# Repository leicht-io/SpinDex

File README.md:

# SpinDex
SpinDex is a small RPM measurement tool for the Beogram 4000 series.
The main focus is to verify that the turntable is restored correctly and maintains the correct speed over an extended period.
The code is written to run on the M5Stack StampS3 (ESP32-S3) but could easily be ported to other microcontrollers and architectures.

This mono repository is divided into multiple sub-repositories, explained below:

### 3D Files (3d-files):
This folder contains the printable enclosure:
- `spindex_bottom.stl`: the base. It holds the electronics and sensor, and its curved jaw hooks onto the turntable chassis.
- `spindex_top.stl`: the lid.
- `spindex_spacer.stl`: an optional insert (about 2.8 mm thick) that clips into the base's jaw. The chassis width differs between production variants of the Beogram 4000, 4002 and 4004: print the base as-is for one width, and add the spacer to fit the other.

| Exploded: lid, base and spacer | Assembled with the spacer fitted |
|---|---|
|  |  |

---

### Web App (web-app)
This folder contains the web app. It connects to the controller over Bluetooth (Web Bluetooth) or a USB cable (Web Serial), with nothing to install, and records, organises and compares RPM measurements. It's hosted publicly, free to use, at **https://spindex.leicht.io/**.

Features:
- **Desktop-style layout**: a menu bar (File / Measurement / View), a library sidebar and a status bar showing the link (Bluetooth or USB) and the sensor's firmware version, a live recording readout, the app version and a clock.
- **Bluetooth or USB**: pick how to connect from the connection menu at the top right. Picking one drops the other, so readings are never recorded twice. The status bar warns when the sensor is connected but sends no readings.
- **Turntable folders**: measurements are grouped per turntable, identified by model and serial number (e.g. "Beogram 4002 · SN 2145678"). Pick or create the turntable when starting a measurement; typing an existing model/serial files it with the earlier runs. Search the library by name or serial.
- **Recording**: start/stop measurements, persisted locally in the browser (IndexedDB), so a page refresh or reconnect doesn't lose a running session. Automatic reconnect rides out a dropped Bluetooth link during an unattended run. Over USB, a cable pulled mid-session reconnects by itself when it's plugged back in, and a page reload during a recording picks the sensor back up without the picker. Otherwise an idle tab leaves the port alone for other tools.
- **Measurement view**: current/average/peak readouts with their deviation from the nominal 33⅓/45 RPM on a small gauge, colour-coded by how far off spec, plus a chart that zooms to the measured range and marks the nominal speed.
- **Chart time windows** (Live 10 min / 1h / 6h / 12h / 24h / All), auto-bucketed to a fixed point budget so even a 24h session stays smooth.
- **Gap-aware charting**: a disconnect or closed tab shows as a marked gap rather than a misleading flat or interpolated line.
- **Compare**: overlay up to eight measurements aligned by time since start (e.g. before/after a belt change), with a hover readout and a stats table: mean, drift from nominal, rev-to-rev standard deviation, min and max, ignoring spin-up and stopped readings.
- **Organise**: rename, move between folders, export as CSV, delete.
- **Connection help**: a dialog explains how to connect over Bluetooth and over USB on the current platform, with a table of which browsers support each. Browsing and comparing saved measurements works in any browser; only recording needs Web Bluetooth or Web Serial.
- **Changelog**: click the version in the status bar.
- **Sensor firmware updates**: *Update sensor firmware…* in the connection menu flashes firmware over USB, through the chip's own bootloader, so it works whatever the sensor runs now. It offers every firmware release: the one for this version of the app by default, or an older one to downgrade (see below).
- Works from phone to desktop: below 900px the library becomes a drawer, and below 720px the menus fold into one overflow menu.
- Dark, instrument-style design after the leicht.io look: IBM Plex Sans / Plex Mono and a copper accent.

Browser support for recording:

| Browser | Platforms | Bluetooth (Web Bluetooth) | USB (Web Serial) |
|---|---|---|---|
| Google Chrome | Windows 10+, macOS, ChromeOS | ✓ | ✓ |
| Google Chrome | Linux | behind `chrome://flags/#enable-experimental-web-platform-features`, BlueZ 5.41+ | ✓ (needs access to `/dev/ttyACM*`, usually the `dialout` group; see the note below) |
| Google Chrome | Android 6+ | ✓ | only on some newer devices |
| Microsoft Edge | Windows, macOS | ✓ | ✓ |
| Firefox | Windows, macOS, Linux | ✕ | ✓ (151+) |
| Opera | Windows, macOS, Linux | ✕ | ✓ |
| Samsung Internet, Opera | Android | ✓ | ✕ |
| Bluefy | iPhone, iPad | ✓ (third-party app) | ✕ |
| Safari | all | ✕ | ✕ |

USB needs firmware built from this repository at or after USB support was added (see the µController section). Older firmware connects over USB but sends no readings. In the port picker the sensor is listed as *USB JTAG/serial debug unit*, a name fixed in the ESP32-S3 (see the µController section).

Chrome on Linux, in versions before Chromium's September 2026 fix, can drop the port the moment it opens it (the app says "the port was dropped right after opening it"). That happens after a pyserial-based tool (PlatformIO's upload or `pio device monitor`, esptool) has used the port, because those tools leave it with `VMIN=0` and Linux keeps that setting for the next program. Run `stty -F /dev/ttyACM0 min 1` and connect again. A PlatformIO upload does this for you (see below).

Measurements are stored per browser; export as CSV to move them elsewhere.

Development, from `web-app/`:
- `yarn start`: dev server (HTTPS, required for Web Bluetooth and Web Serial).
- `yarn build`: production build.
- `yarn test`: unit tests for the pure logic (chart bucketing/gap detection, CSV export, measurement stats, folder grouping, USB serial line parsing, changelog/version consistency).

Releases are listed in `web-app/app/core/changelog.ts`. Its newest entry must match the `version` in `web-app/package.json` (a unit test checks this), so bump both together.

`yarn build` also builds the sensor firmware from your working copy with PlatformIO (`pio` on the PATH, its own install in `~/.platformio`, or `PIO=/path/to/pio`). It puts the firmware in `dist/firmware/<version>/`, where the firmware updater loads it from, next to the older releases' firmware from GitHub if GitHub can be reached. `dist/` is gitignored, so this build is only for deploying or serving from your machine; released builds come from the Release workflow below. Browsers can't download GitHub release files from another site, so the app serves all firmware itself. `yarn build:web` builds the app alone.

#### Releases

Releases are automatic, driven by [conventional commits](https://www.conventionalcommits.org/) on master (`.github/workflows/release.yml`):

1. After each push to master, the *Release* workflow opens or updates a **release PR**. It bumps the version from the commits since the last release (`feat`: minor; `fix`, `perf`: patch; `feat!:` or a `BREAKING CHANGE:` footer: major; `docs`, `chore`, `ci`, `test` and `refactor` don't release) and drafts the entry in `web-app/app/core/changelog.ts` from the commit subjects.
2. Edit that entry into user-facing wording (the app shows it as release notes), then merge the PR. Once you've pushed to the PR, the workflow leaves it alone.
3. The merge publishes the release: tests, the `v<version>` tag, and a GitHub release with notes from the changelog. It carries the firmware files (for the updater, and for flashing by hand) and `spindex-web-<version>.zip`, the built app with every firmware release in it.
4. Upload the contents of that zip to the host.

A version bumped by hand (in `package.json` and `changelog.ts`) is published the same way once it reaches master. With squash merges, the PR title becomes the commit, so give PRs conventional titles too.

The workflow needs, under *Settings → Actions → General → Workflow permissions*, "Read and write permissions" and "Allow GitHub Actions to create and approve pull requests". The *CI* workflow (`.github/workflows/ci.yml`) checks every pull request: types, lint, tests and builds of the app and the firmware. Release PRs opened by the bot don't trigger it (GitHub doesn't run workflows for its own token's PRs), so publishing runs the tests itself. Dependabot (`.github/dependabot.yml`) proposes npm and Actions updates weekly.

To try updates with `yarn start`, run `yarn firmware:local` (the working copy's firmware, as `yarn build` bundles it) or `yarn firmware` (only the GitHub releases) first; without either, the updater says the build has no firmware.

---

### µController Source Code (controller-source)
This folder contains the source code for the microcontroller. The RPM edge-counting/calculation logic is split out into a hardware-free class (`src/logic/RpmCounter`) with its own unit tests, runnable on the host (no board needed) via `pio test -e native`.

Every 500 ms the firmware sends the current RPM two ways: as a Bluetooth notification, and as a line like `rpm:33.33` on the StampS3's own USB-C port. The web app reads those lines over Web Serial, and `pio device monitor` or the Arduino Serial Plotter can show them too.

The firmware's version is the web app's: `scripts/firmware_version.py` reads it from `web-app/package.json` at build time, so a release bumps one number (see the web app section) and the sensor reports the version of the app it shipped with. The web app reads it on connecting and shows it in the status bar. Over Bluetooth it's the Firmware Revision String (`0x2A26`) in the standard Device Information Service (`0x180A`). Over USB the app sends a `version` line and the firmware answers with a line like `version:2.3.0`, which it also prints on startup. You can type `version` into `pio device monitor` to check it. Firmware from before 2.3.0 doesn't report a version, and the app shows it as unknown. Firmware built without `web-app/package.json` next to it reports `unversioned`.

USB uses the ESP32-S3's built-in USB-Serial/JTAG unit (`ARDUINO_USB_CDC_ON_BOOT` in `platformio.ini`), which keeps uploads button-free. Its name, "USB JTAG/serial debug unit", is fixed in the chip. Only the USB-OTG controller (TinyUSB) could call the device "SpinDex", but on the pinned Arduino core its reboot-to-bootloader hangs the board, so every upload would need the G0 button.

After each upload, `scripts/restore_tty.py` sets the port back to `VMIN=1` on Linux so Chrome can read it (see the Linux note in the web app section). After using `pio device monitor`, run `stty -F /dev/ttyACM0 min 1` yourself.

A browser connected to the sensor holds its port, so choose **Disconnect** in the app (or close it) before uploading.

`pio run -t webbundle` (with `SPINDEX_FIRMWARE_DIR` set) copies what an upload flashes into a folder, with a `manifest.json` of offsets and flash settings: bootloader, partition table, `boot_app0` and the app. The *Release* workflow runs it for each release and attaches the result to the GitHub release; `yarn firmware:local` runs it on the working copy. The web app's updater flashes exactly that set with esptool-js. Writing `boot_app0` resets which app slot boots, so the sensor always starts the image just written. The manifest carries each image's size and SHA-256, which the app checks after downloading (a missing or stale file is never flashed), and esptool-js reads every image back from flash to verify it. Before writing, the updater checks the board is an ESP32-S3 with 8 MB of flash, since other ESP32-S3 boards share the SpinDex's USB IDs.

---

### Documentation (documentation)
This folder contains the [sensor pin setup and wiring diagram](documentation/pinSetup.md). The PCB schematics themselves live in `hardware/carrier-board`, below.

---

### Hardware (hardware/carrier-board)
This folder contains the custom carrier board PCB design (KiCad) that
piggybacks the M5Stack StampS3 module and the TCRT5000 IR sensor front end
on a single board. See its own [README](hardware/carrier-board/README.md)
for the schematic writeup, BOM, and what's left before fabrication.

---

Please note that this project is in progress and prone to change. The following tasks needs to be implemented before i consider the SpinDex finished.

- tests (started — see the web app's `yarn test` and the µController's `pio test -e native`; coverage is still thin, mostly the pure logic so far).
- custom-made PCB (in progress, see `hardware/carrier-board` — not yet routed or fabricated).

Feel free to develop further on the project and create PRs if, necessary. I would be happy to cooperate with others on the device.

More pictures and background: [SpinDex on leicht.io](https://leicht.io/restoration-services#spindex).

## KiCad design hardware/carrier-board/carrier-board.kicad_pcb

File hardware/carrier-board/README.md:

# SpinDex Carrier Board

A custom PCB that piggybacks the M5Stack STAMP-S3M module on one side and
implements the TCRT5000 reflective IR sensor + comparator circuit directly
on the other, replacing the hand-wired FC-51/TCRT5000 breakout + jumper
wires with a single board sized to mount precisely against the Beogram's
strobe ring.

Built with KiCad 9. Everything in this folder was generated by script (see
"How this was built" below) and validated with `kicad-cli` (ERC/DRC both
pass clean) — **but it has not been opened in the KiCad GUI or physically
verified yet.** Do the checks in "Before you fabricate" first.

## Files

- `carrier-board.kicad_pro` / `.kicad_sch` / `.kicad_pcb` — the project
- `spindex.kicad_sym` — custom symbols: `STAMP-S3M`, `TCRT5000`
- `spindex.pretty/STAMP-S3M_DIP28_P1.27mm.kicad_mod` — custom footprint
- `sym-lib-table` / `fp-lib-table` — project-local library table, adds only
  the `spindex` library; everything else (Device, Comparator, OptoDevice,
  Connector_JST, etc.) resolves from KiCad's standard global libraries

## What's verified vs. estimated

**Verified directly from primary sources:**
- STAMP-S3M's full 28-pin pinout (pin number → signal name) — read
  directly from M5Stack's own module schematic
  ([Sch_M5StampS3_v0.2.pdf](https://m5stack-doc.oss-cn-shenzhen.aliyuncs.com/522/Sch_M5StampS3_v0.2.pdf))
- 1.27mm pin pitch, 26×18×5mm module body (M5Stack docs/product listings)
- TCRT5000 pin assignment (1=Collector, 2=Emitter, 3=Anode, 4=Cathode) —
  read directly from the [Vishay TCRT5000 datasheet](https://www.vishay.com/docs/83760/tcrt5000.pdf)'s
  top-view pin diagram
- The `OptoDevice:Vishay_TCRT5000` footprint is KiCad's own standard
  library part for this exact component — not custom-made

**NOT verified — check before fabricating:**
- **Row-to-row pad spacing on `STAMP-S3M_DIP28_P1.27mm`, set to 15.24mm.**
  No source gives this dimension; it's sized to fit inside the module's
  known 18mm body width with plausible margin, nothing more. **Measure the
  actual module with calipers and update `ROW_SPACING` in
  `gen_footprint.py` (or edit the footprint directly) before ordering
  boards.** Getting this wrong means the module's pins won't line up with
  the holes.

## The circuit

- **Power:** none of this board's business, deliberately. The M5StampS3
  module (the assembled product, not just the bare chip-module inside it)
  has its own onboard USB-C connector and 5V→3.3V regulator — confirmed
  from M5Stack's own schematic, which shows the USB-C port, ESD protection,
  and DCDC regulator as part of the same board the 28-pin header lives on.
  Power it over USB-C like you would to flash it, and its `3V3` pin (typed
  `power_out` in the symbol, since the module is genuinely sourcing that
  rail) feeds the sensor circuit directly. `5V` on the header is a no-connect
  here — it's an available breakout on the module, not something this board
  drives. There's no separate power connector or regulator on this board at
  all; earlier drafts had a JST-PH power input and a bulk cap, both removed
  once it was clear the module's own USB-C already covers it.
- **Sensor front end:** D1 (TCRT5000) — R1 (220Ω) limits the IR LED
  current; R2 (10kΞ) pulls the phototransistor's collector up to 3V3,
  forming a voltage divider whose node (`PHOTO_C`) swings toward GND when
  a reflective bar is under the sensor.
- **Comparator:** U2 (LM393, referenced via its base `LM2903` symbol —
  same part, see below) compares `PHOTO_C` against a threshold set by
  RV1 (10kΩ trimmer, wired 3V3–GND with the wiper feeding the comparator's
  `-` input). Output idles HIGH (pulled up by R4) and drops LOW when a
  reflective bar is detected — **same polarity as the wired TCRT1000/FC-51
  setups this replaces, so `arduino_target.ino`'s edge-detection logic
  works unchanged.** The comparator's second (unused) gate has both inputs
  tied to GND so it can't float/oscillate; its output is left unconnected.
- **Status LED:** D2 + R3, lights when the sensor output is LOW (i.e. a
  bar is detected) — handy for bench-checking alignment without a scope.
- **EN/Boot pull-ups, no buttons:** R5 (10kΩ, `EN`) and R6 (10kΩ, `G0/Boot`)
  hold both pins at a defined HIGH so the module boots and runs normally.
  No manual reset/boot-select switches on this board — flashing means
  reconnecting USB-C to the module directly (same as any bare module),
  not pressing a button here.

### Why `Comparator:LM2903` instead of `LM393`

KiCad's `LM393` symbol is defined via `(extends "LM2903")` — it only holds
property overrides and depends on `LM2903`'s own graphics/pins to actually
render. Referencing `LM2903` directly avoids needing to also embed the
base symbol just to satisfy the alias, while remaining the same physically
interchangeable dual-comparator part; the schematic's `Value` field is set
to "LM393" so the BOM reads correctly.

## Layout

Two zones, as asked for — StampS3 on the left, TCRT5000 + comparator front
end on the right, on one board:

```
[R5]                        [D1 TCRT5000]
[R6]       [U1 STAMP-S3M]   [R1][R2]
                            [RV1]
                            [U2 LM393][C2]
                            [R4][R3]
                            [D2 status]
```

The board outline is currently just a bounding rectangle around all
components with room to breathe — **not a final shape.** Once the
enclosure is designed (or if it already exists in `../../3d-files/`),
reshape `Edge.Cuts` in the PCB editor so the sensor end sits where the
enclosure needs it relative to the platter, then trim the rest of the
board down from there.

## Before you fabricate

1. **Measure the actual STAMP-S3M module with calipers** and correct
   `ROW_SPACING` in `spindex.pretty/STAMP-S3M_DIP28_P1.27mm.kicad_mod` if
   it doesn't match 15.24mm.
2. **Open in KiCad and run "Update PCB from Schematic"** (Tools menu, or
   the equivalent toolbar button) — this syncs the netlist from the
   ERC-clean schematic onto the PCB and lights up the ratsnest. This
   wasn't done here on purpose: hand-duplicating the netlist into the PCB
   file risked a silent mismatch between the two; letting KiCad's own
   sync do it means there's exactly one source of truth (the schematic).
3. **Route the board.** Nothing is routed yet — only placed. A scripted
   auto-routing attempt was made (A* pathfinding with F.Cu/B.Cu+via
   fallback for congested spots) and got every net to *find* a path with
   0 unconnected nets, but kept surfacing new clearance/via-crowding
   violations faster than they could be cleanly resolved blindly —
   routing is fundamentally an interactive, visual-feedback problem
   (that's why every PCB tool has a live-DRC GUI for it) in a way
   placement and schematic capture weren't, and continuing to iterate
   on it without that feedback stopped being productive. With 12
   components and mostly low-speed signals this is a reasonable board to
   route by hand in an evening — KiCad's interactive router (push-and-
   shove, hotkey `X`) makes this fast once nets are synced from the
   schematic (step 2). There's no RF-critical routing here *except* keep
   the area over the STAMP-S3M module's antenna (top-right corner of its
   footprint, matching its silkscreen orientation) clear of copper and
   other components per M5Stack's own schematic — check their PDF for
   the exact keepout if you want to be precise about it. Also worth
   knowing: the layout was widened from an earlier pass to make room
   once real pad sizes were checked (routing revealed the initial
   spacing was tighter than the components actually need) — reasonable
   starting positions, not final.
4. **Tidy the schematic visually.** It's electrically correct (0 ERC
   violations) but was laid out programmatically — labels and component
   text overlap in places. Purely cosmetic; a few minutes of dragging
   things apart in the schematic editor fixes it, no netlist risk.
5. Reshape the board outline to the final enclosure, as above.
6. Re-run `kicad-cli sch erc` / `kicad-cli pcb drc` after any changes.

## BOM

| Ref | Part | Value | Footprint |
|---|---|---|---|
| U1 | M5Stack STAMP-S3M | — | `spindex:STAMP-S3M_DIP28_P1.27mm` |
| D1 | Vishay TCRT5000 | — | `OptoDevice:Vishay_TCRT5000` |
| U2 | LM393 (or LM2903) | dual comparator | `Package_DIP:DIP-8_W7.62mm` |
| RV1 | Trimmer potentiometer | 10kΩ | `Potentiometer_THT:Potentiometer_Bourns_3296W_Vertical` |
| R1, R3 | Resistor | 220Ω | `Resistor_THT:R_Axial_DIN0207_L6.3mm_D2.5mm_P10.16mm_Horizontal` |
| R2, R4, R5, R6 | Resistor | 10kΩ | same |
| C2 | Ceramic capacitor | 100nF | `Capacitor_THT:C_Disc_D3.0mm_W2.0mm_P2.50mm` |
| D2 | LED (status) | — | `LED_THT:LED_D3.0mm` |

All through-hole, hand-solder friendly. No power connector, regulator, or
buttons on this board — power and programming both go through the
M5StampS3 module's own USB-C port. Total BOM cost is a couple of dollars
in passives plus the STAMP-S3M module and TCRT5000 sensor themselves.

## How this was built

Every file here was generated by small Python scripts rather than
hand-typed — KiCad's `.kicad_sym`/`.kicad_sch`/`.kicad_pcb` S-expression
formats are precise enough that hand-authoring them risks subtle,
hard-to-spot mistakes (a wrong fill-type value, a flipped Y-axis sign
between library space and page space) that only show up as ERC/DRC
failures or, worse, silently-wrong connectivity. The generator scripts
aren't included in this folder (they were scratch tooling, not something
meant to be re-run), but the process was: generate → validate with
`kicad-cli sch erc` / `kicad-cli pcb drc` → fix → repeat until both came
back clean, plus rendering to SVG/PNG at each stage to visually sanity
check symbol/footprint graphics. Final state: **0 ERC violations, 0 DRC
violations.**

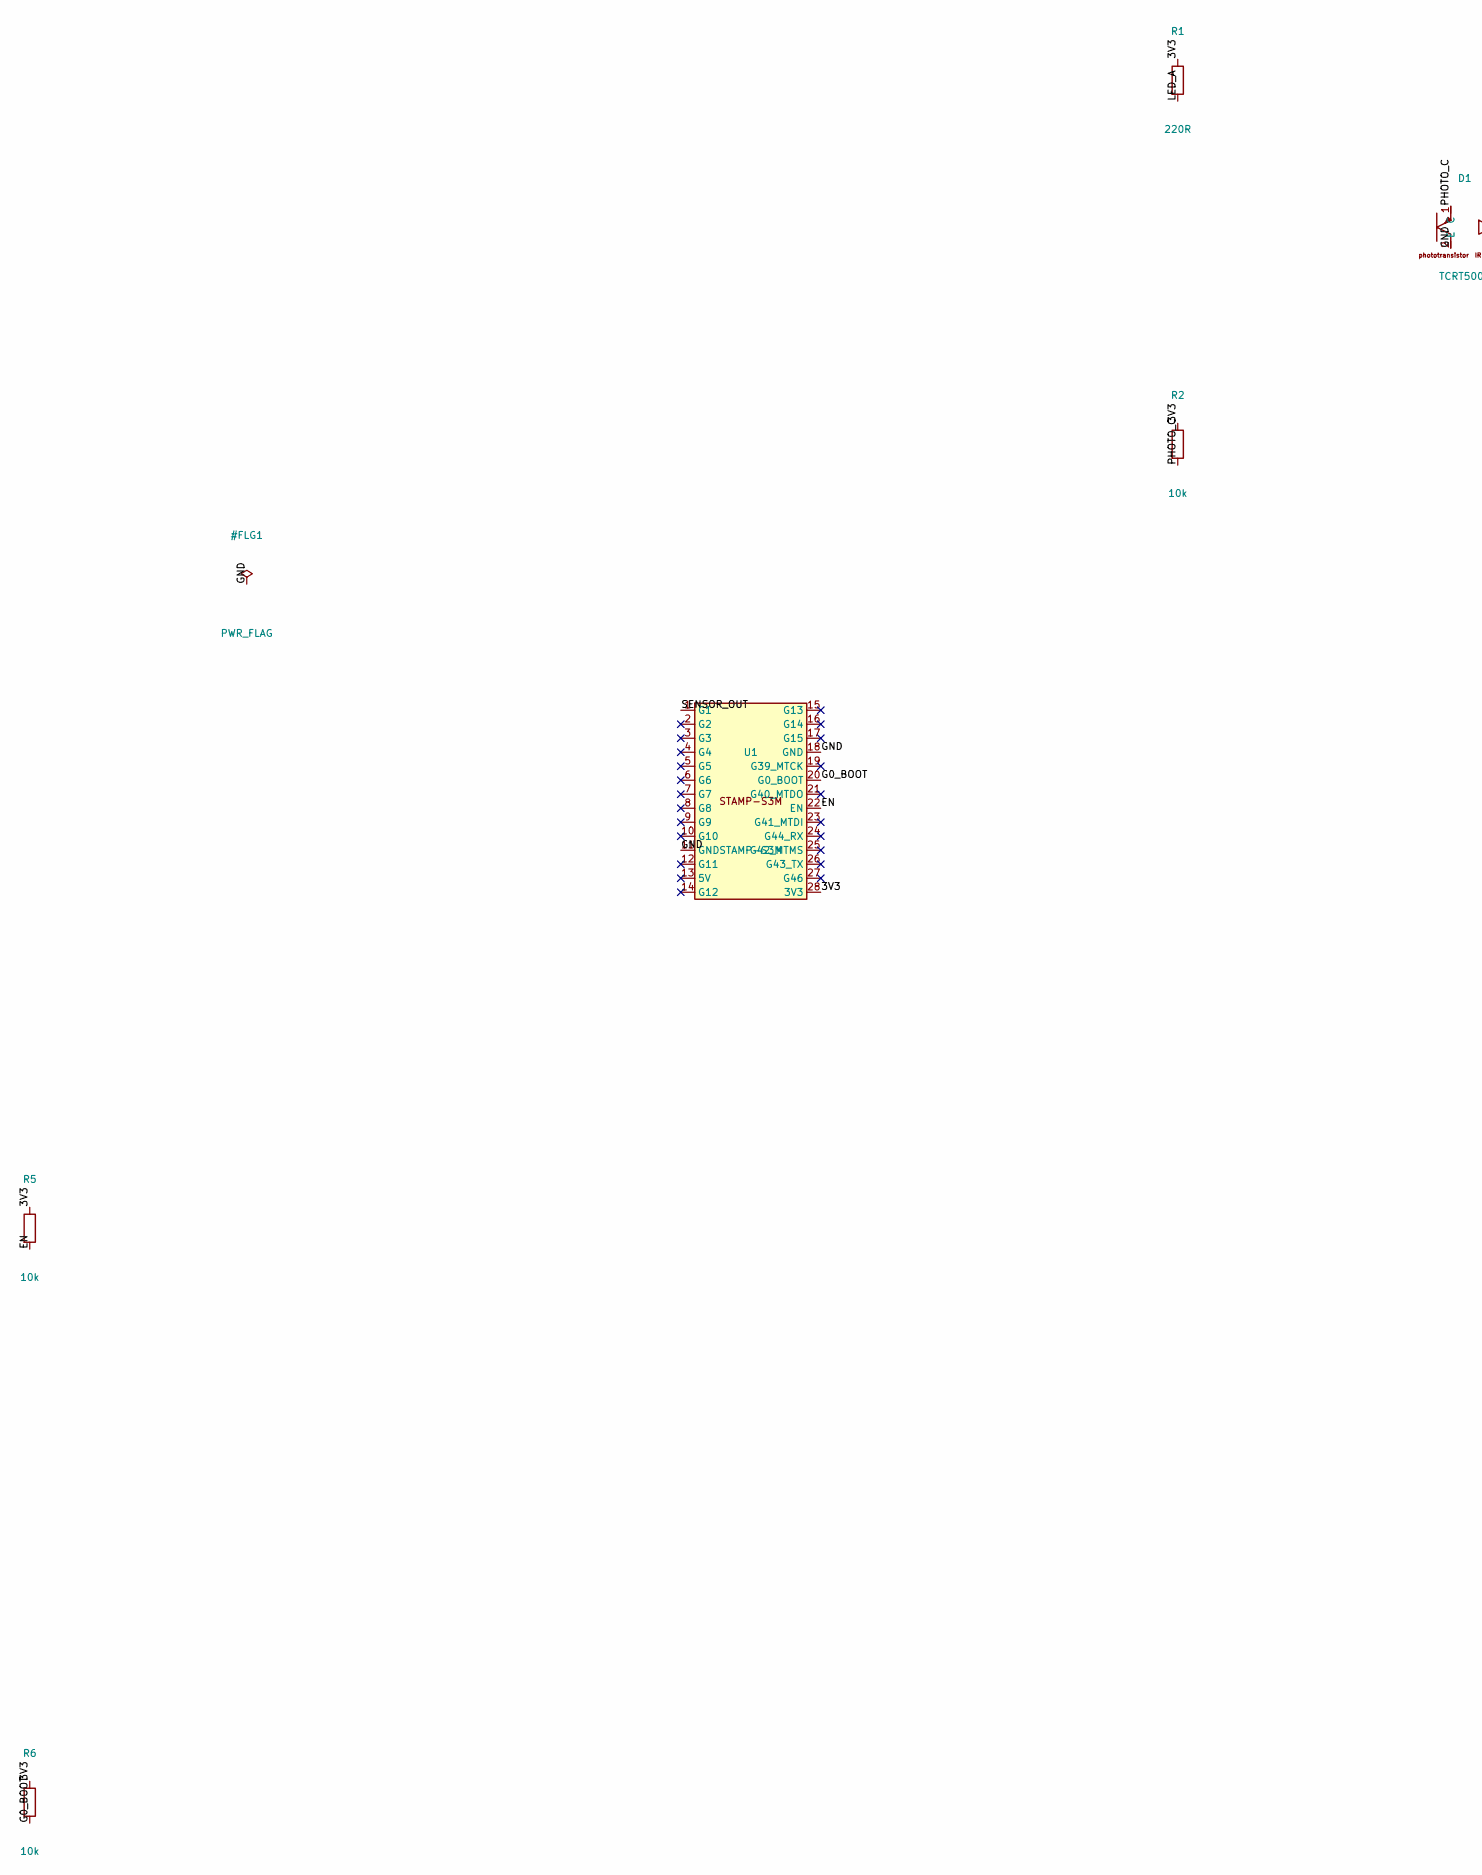
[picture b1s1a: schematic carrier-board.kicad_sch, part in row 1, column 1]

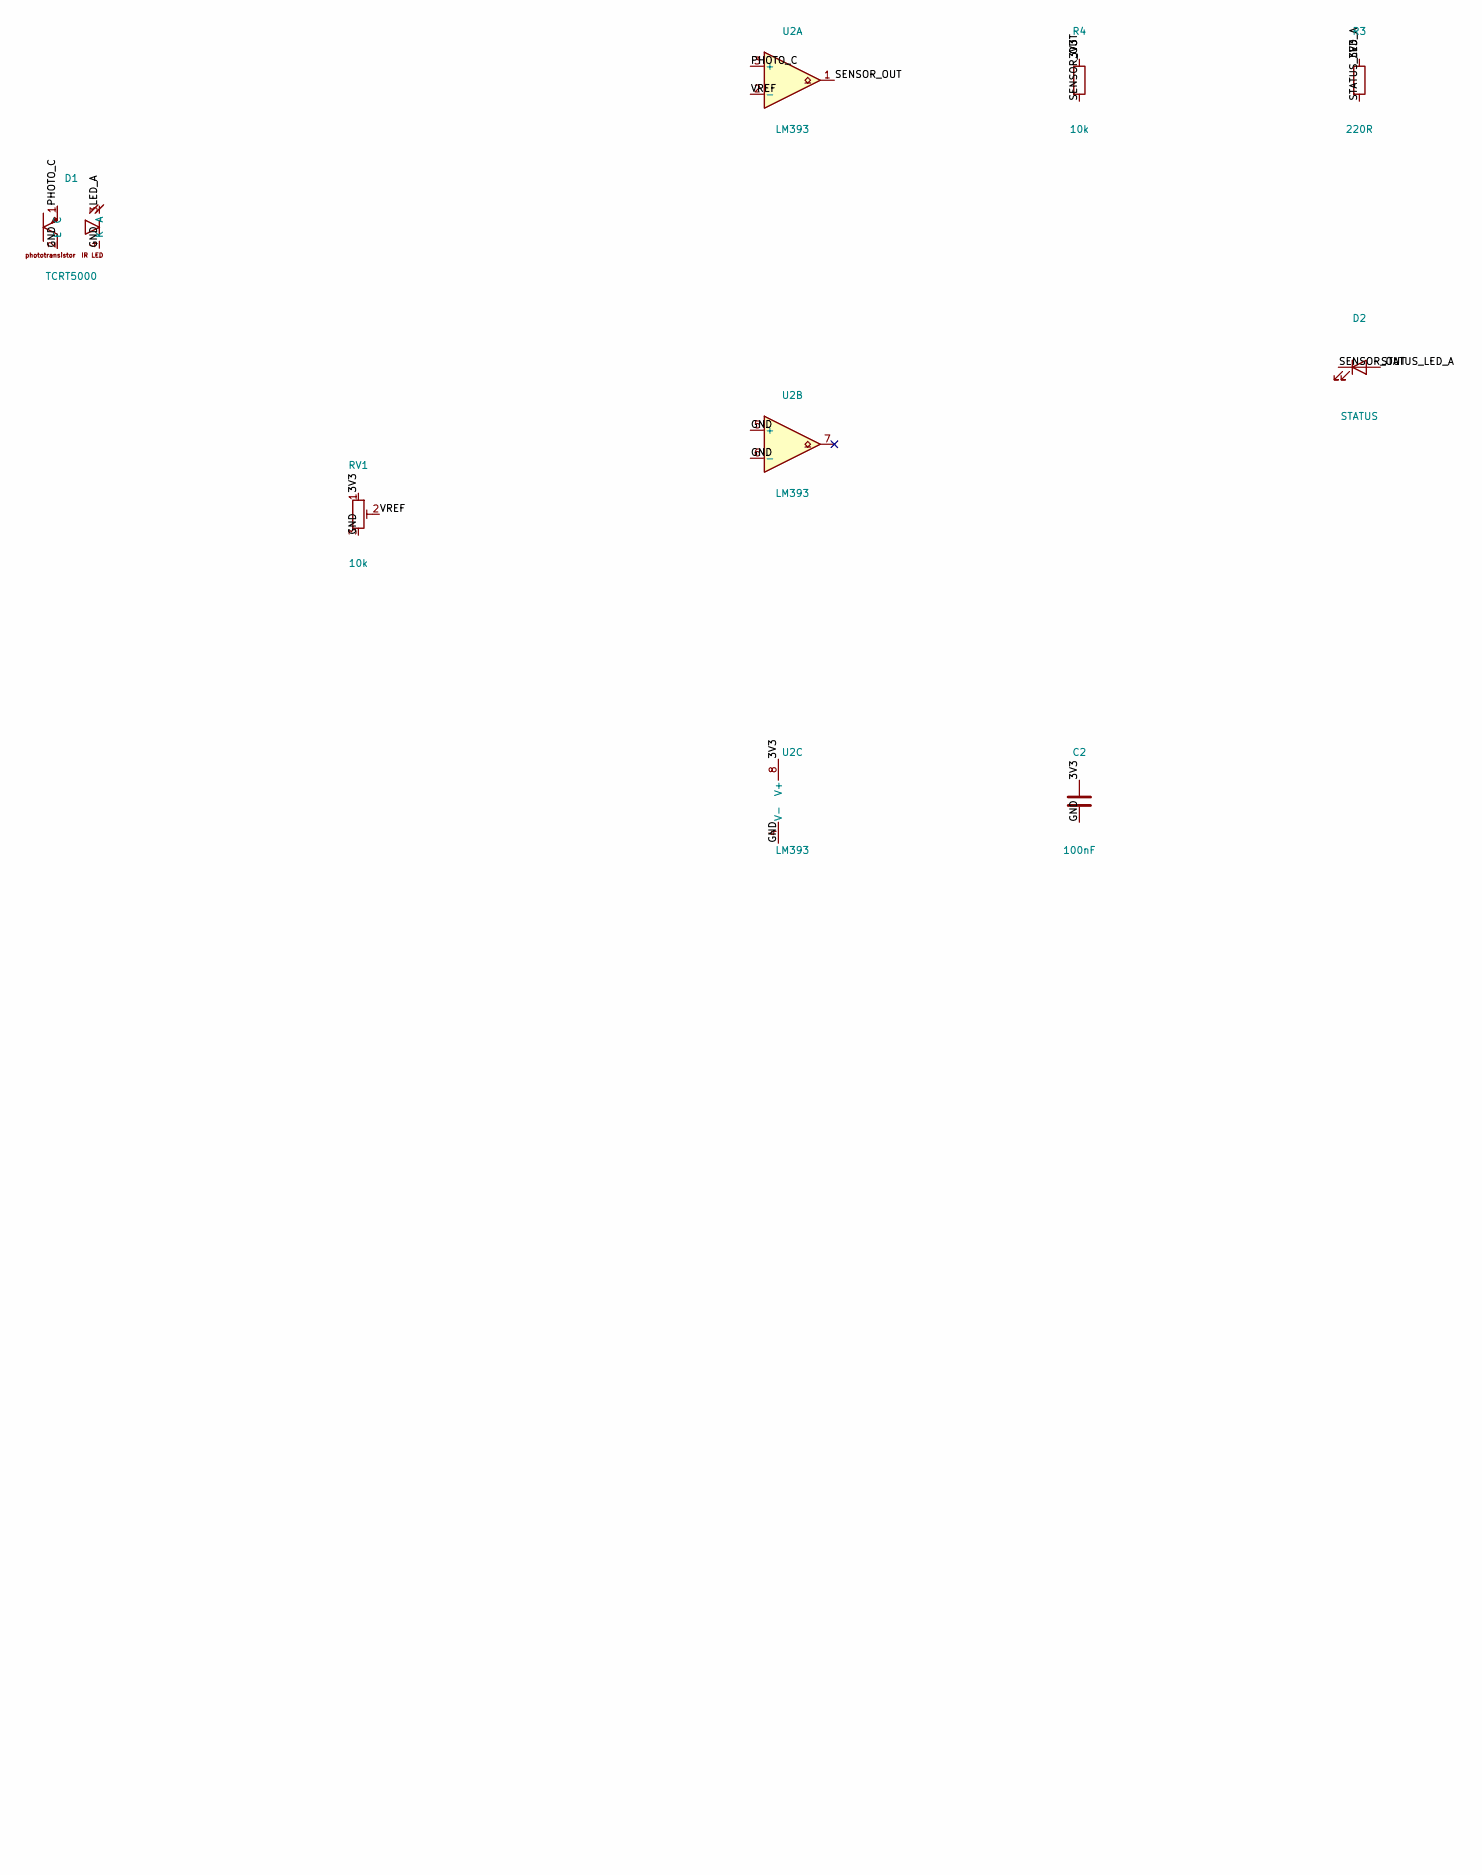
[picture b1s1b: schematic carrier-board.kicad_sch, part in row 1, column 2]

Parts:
C2: 100nF; C_Disc_D3.0mm_W2.0mm_P2.50mm
D1: TCRT5000; Vishay_TCRT5000
D2: STATUS; LED_D3.0mm
R1, R3: 220R; R_Axial_DIN0207_L6.3mm_D2.5mm_P10.16mm_Horizontal
R2, R4, R5, R6: 10k; R_Axial_DIN0207_L6.3mm_D2.5mm_P10.16mm_Horizontal
RV1: 10k; Potentiometer_Bourns_3296W_Vertical
U1: STAMP-S3M; Stamp-S3-SMD
U2: LM393; DIP-8_W7.62mm

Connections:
/3V3: C2.1, R1.1, R2.1, R3.1, R4.1, R5.1, R6.1, RV1.1, U1.28 (3V3), U2.8 (V+)
/EN: R5.2, U1.22 (EN)
/G0_BOOT: R6.2, U1.20 (G0_BOOT)
/GND: C2.2, D1.2 (E), D1.4 (K), RV1.3, U1.11 (GND), U1.18 (GND), U2.4 (V-), U2.5 (+), U2.6 (-)
/LED_A: D1.3 (A), R1.2
/PHOTO_C: D1.1 (C), R2.2, U2.3 (+)
/SENSOR_OUT: D2.1 (K), R4.2, U1.1 (G1), U2.1
/STATUS_LED_A: D2.2 (A), R3.2
/VREF: RV1.2, U2.2 (-)

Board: 2 copper layers, 12 parts (1 on the bottom side), 9 nets, no tracks yet.

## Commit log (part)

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2019-11-04 added: initial commit.
2019-11-04 refactor: Splitted into multiple project folders
2019-11-04 started implementing desktop client
2019-11-05 refactor: added Electron client
2019-11-05 fix: updated .gitignore
2019-11-05 Added API config
2019-11-06 refactor: added new components
2019-11-06 fix: added new API endpoints.
2019-11-07 fix: added yesterdays changes..
2019-11-11 bugfixes
2019-11-11 updated source for arduino
2019-11-17 fix: added font and removed evergreen ui library.
2019-11-17 refactor: removed REST API in favor of WebSockets.
2019-11-18 refactor: added automatic serial path selection based on venderId and partId.
2019-11-22 Added WWSSS
2019-11-23 Added new version
2019-11-26 bufixes
2019-11-27 added working copy of arduino code.
2019-11-27 fix: added temperature to API structure.
2019-12-05 fix: added icons to Electron app.
2019-12-20 feat: introduced SASS variables.
2020-01-13 Fixed screen resolution.
2020-01-29 fixes
2020-02-03 bugfix
2020-02-03 updated client
2020-02-04 feat: added software keyboard.
2020-02-04 updated source code
2020-02-13 converted to Platform.io
2020-02-13 feat: added new splashscreen.
2020-02-14 fiux
2020-03-06 added shurtdown icon
2022-11-06 chore: refactored docs.
2022-11-29 feat: updated dependencies and cleaned solution.
2022-11-29 chore: refactored solution.
2022-12-16 chore: updated docs and refactored solution.
2022-12-16 feat: added android app skeleton.
2022-12-16 refactor: updated documentation.
2022-12-20 feat: added support for CLion IDE.
2022-12-21 fix: updated RPM calculations.
2022-12-22 feat: (WIP) added multicore support for ESP32 and ST7735 SPI display.
2022-12-23 chore: added todos.
2022-12-27 feat: added BL support.
2023-05-07 chore(deps): bump sqlite3 from 5.1.4 to 5.1.5 in /desktop-app
    Bumps [sqlite3](https://github.com/TryGhost/node-sqlite3) from 5.1.4 to 5.1.5.
    - [Release notes](https://github.com/TryGhost/node-sqlite3/releases)
    - [Commits](https://github.com/TryGhost/node-sqlite3/compare/v5.1.4...v5.1.5)
    ---
    updated-dependencies:
    - dependency-name: sqlite3
2023-05-07 chore(deps): bump json5 from 2.2.1 to 2.2.3 in /desktop-app
    Bumps [json5](https://github.com/json5/json5) from 2.2.1 to 2.2.3.
    - [Release notes](https://github.com/json5/json5/releases)
    - [Changelog](https://github.com/json5/json5/blob/main/CHANGELOG.md)
    - [Commits](https://github.com/json5/json5/compare/v2.2.1...v2.2.3)
    ---
    updated-dependencies:
2023-05-07 chore(deps): bump http-cache-semantics in /desktop-app
    Bumps [http-cache-semantics](https://github.com/kornelski/http-cache-semantics) from 4.1.0 to 4.1.1.
    - [Commits](https://github.com/kornelski/http-cache-semantics/compare/v4.1.0...v4.1.1)
    ---
    updated-dependencies:
    - dependency-name: http-cache-semantics
    dependency-type: indirect
2023-05-07 chore(deps): bump sequelize from 6.28.0 to 6.29.0 in /desktop-app
    Bumps [sequelize](https://github.com/sequelize/sequelize) from 6.28.0 to 6.29.0.
    - [Release notes](https://github.com/sequelize/sequelize/releases)
    - [Commits](https://github.com/sequelize/sequelize/compare/v6.28.0...v6.29.0)
    ---
    updated-dependencies:
    - dependency-name: sequelize
2023-05-07 chore(deps): bump d3-color and recharts in /desktop-app
    Bumps [d3-color](https://github.com/d3/d3-color) to 3.1.0 and updates ancestor dependency [recharts](https://github.com/recharts/recharts). These dependencies need to be updated together.
    Updates `d3-color` from 2.0.0 to 3.1.0
    - [Release notes](https://github.com/d3/d3-color/releases)
    - [Commits](https://github.com/d3/d3-color/compare/v2.0.0...v3.1.0)
    Updates `recharts` from 2.2.0 to 2.5.0
    - [Release notes](https://github.com/recharts/recharts/releases)
2023-12-26 fix: getting ready for headless.
2023-12-26 feat: updated docs.
2023-12-30 fix: cleaned solution and made it ready for web BLE.
2023-12-30 chore: updated docs and moved folder.
2023-12-31 chore: refactored controller source code.
2023-12-31 chore: refactored webapp code.
2023-12-31 feat: sending zero if nothing is measured.
2023-12-31 chore: refactored.
2024-01-01 feat: converted code to use ISR.
2024-01-01 chore: refactored controller source.
2024-01-01 chore: refactored webapp source.
2024-01-07 feat: removed the Android app.
2024-01-07 feat: updated naming.
2024-01-11 chore: updated docs.
2024-12-15 chore:
